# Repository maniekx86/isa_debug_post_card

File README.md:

# ISA debug post card
ISA debug post card with additional features like data/address bus analyzer, frequency measure and multi I/O POST port selection. Uses a XC95144XL CPLD as main IC. Dedicated project page with manual and assembly instructions will be available soon.

It is also designed to have a 45-degree bevel at the connector. When ordering, enable edge connector and a 45-degree bevel. Ready gerbers are available in output folder

CPLD VHDL source code and compiled firmware for the CPLD are available here: https://github.com/maniekx86/isa_debug_post_card_cpld_source

Based on https://github.com/JayesonLS/ISA-Cards IsaTemplate

## Special thanks to [PCBWay](https://www.pcbway.com)!

Special thanks to PCBWay for sponsoring this project! PCBWay is a well-known PCB prototyping and manufacturing service, providing high-quality boards and excellent customer support. I have worked with their boards in the past and can say that they are of great quality. I easily placed an order for PCBs on their platform for this project without any problems. The sponsorship also included a free quick delivery option. If you’re looking for reliable PCB prototyping and manufacturing services, I highly recommend [checking them](https://www.pcbway.com).

## Photos

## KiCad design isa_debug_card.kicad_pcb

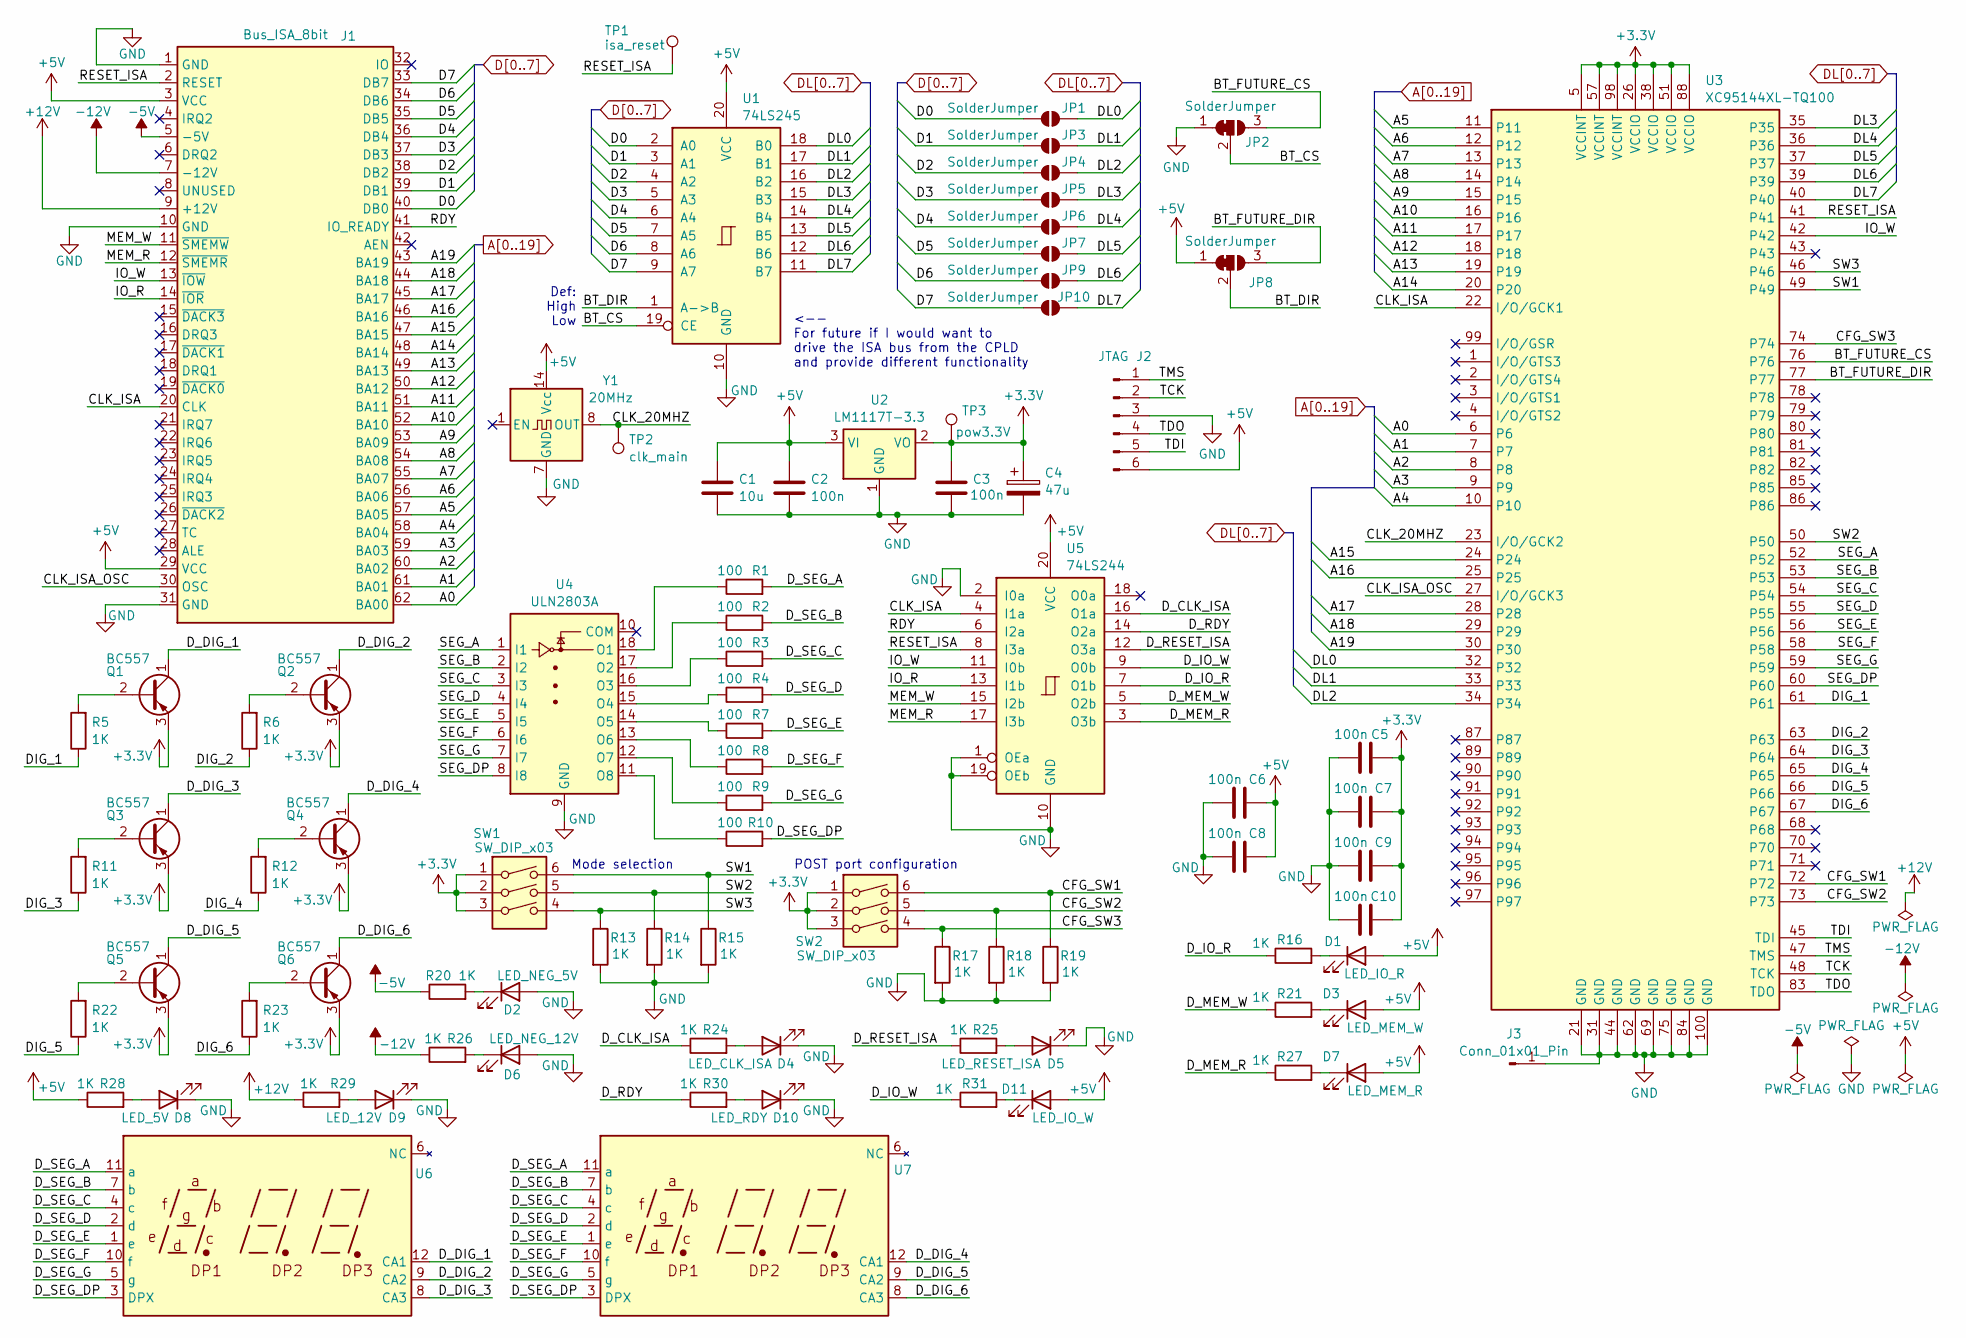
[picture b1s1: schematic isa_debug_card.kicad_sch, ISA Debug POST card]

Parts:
C1: 10u; CP_Radial_D5.0mm_P2.50mm
C2, C3, C5, C6, C7, C8, C9, C10: 100n; C_Disc_D3.0mm_W2.0mm_P2.50mm
C4: 47u; CP_Radial_D5.0mm_P2.50mm
D1: LED_IO_R; LED_D5.0mm
D2: LED_NEG_5V; LED_D5.0mm
D3: LED_MEM_W; LED_D5.0mm
D4: LED_CLK_ISA; LED_D5.0mm
D5: LED_RESET_ISA; LED_D5.0mm
D6: LED_NEG_12V; LED_D5.0mm
D7: LED_MEM_R; LED_D5.0mm
D8: LED_5V; LED_D5.0mm
D9: LED_12V; LED_D5.0mm
D10: LED_RDY; LED_D5.0mm
D11: LED_IO_W; LED_D5.0mm
J1: Bus_ISA_8bit; BUS_XT
J2: JTAG; PinSocket_1x06_P2.54mm_Vertical
J3: Conn_01x01_Pin; PinHeader_1x01_P2.54mm_Vertical
JP1, JP3, JP4, JP5, JP6, JP7, JP9, JP10: SolderJumper; SolderJumper-2_P1.3mm_Open_Pad1.0x1.5mm
JP2, JP8: SolderJumper; SolderJumper-3_P1.3mm_Bridged12_Pad1.0x1.5mm
Q1, Q2, Q3, Q4, Q5, Q6: BC557; TO-92_Inline
R1, R2, R3, R4, R7, R8, R9, R10: 100; R_Axial_DIN0204_L3.6mm_D1.6mm_P7.62mm_Horizontal
R5, R6, R11, R12, R13, R14, R15, R16, R17, R18, R19, R20, R21, R22, R23, R24, R25, R26, R27, R28, R29, R30, R31: 1K; R_Axial_DIN0204_L3.6mm_D1.6mm_P7.62mm_Horizontal
SW1, SW2: SW_DIP_x03; SW_DIP_SPSTx03_Slide_9.78x9.8mm_W7.62mm_P2.54mm
TP1: isa_reset; TestPoint_Pad_2.0x2.0mm
TP2: clk_main; TestPoint_Pad_2.0x2.0mm
TP3: pow3.3V; TestPoint_Pad_2.0x2.0mm
U1: 74LS245; DIP-20_W7.62mm
U2: LM1117T-3.3; TO-220-3_Horizontal_TabDown
U3: XC95144XL-TQ100; TQFP-100_14x14mm_P0.5mm
U4: ULN2803A; DIP-18_W7.62mm
U5: 74LS244; DIP-20_W7.62mm
U6, U7: LED_3_digit_0_56inch_12pin
Y1: 20MHz; OSC_8_14_Multi

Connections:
+3.3V: C3.1, C4.1, C5.2, C7.2, C9.2, C10.2, Q1.3 (E), Q2.3 (E), Q3.3 (E), Q4.3 (E), Q5.3 (E), Q6.3 (E), SW1.1, SW1.2, SW1.3, SW2.1, SW2.2, SW2.3, TP3.1, U2.2 (VO), U3.5 (VCCINT), U3.26 (VCCIO), U3.38 (VCCIO), U3.51 (VCCIO), U3.57 (VCCINT), U3.88 (VCCIO), U3.98 (VCCINT)
+5V: C1.1, C2.1, C6.2, C8.2, D1.2 (A), D3.2 (A), D7.2 (A), D11.2 (A), J1.3 (VCC), J1.29 (VCC), J2.6, JP8.1 (A), R28.1, U1.20 (VCC), U2.3 (VI), U5.20 (VCC), Y1.14 (Vcc)
+12V: J1.9 (+12V), R29.1
-5V: J1.5 (-5V), R20.1
-12V: J1.7 (-12V), R26.1
/BT_CS: JP2.2 (C), U1.19 (CE)
/BT_DIR: JP8.2 (C), U1.1 (A->B)
/BT_FUTURE_CS: JP2.3 (B), U3.76
/BT_FUTURE_DIR: JP8.3 (B), U3.77
/CFG_SW1: R19.1, SW2.6, U3.72
/CFG_SW2: R18.1, SW2.5, U3.73
/CFG_SW3: R17.1, SW2.4, U3.74
/CLK_20MHZ: TP2.1, U3.23 (I/O/GCK2), Y1.8 (OUT)
/CLK_ISA: J1.20 (CLK), U3.22 (I/O/GCK1), U5.4 (I1a)
/CLK_ISA_OSC: J1.30 (OSC), U3.27 (I/O/GCK3)
/DIG_1: R5.1, U3.61
/DIG_2: R6.1, U3.63
/DIG_3: R11.1, U3.64
/DIG_4: R12.1, U3.65
/DIG_5: R22.1, U3.66
/DIG_6: R23.1, U3.67
/D_CLK_ISA: R24.1, U5.16 (O1a)
/D_DIG_1: Q1.1 (C), U6.12 (CA1)
/D_DIG_2: Q2.1 (C), U6.9 (CA2)
/D_DIG_3: Q3.1 (C), U6.8 (CA3)
/D_DIG_4: Q4.1 (C), U7.12 (CA1)
/D_DIG_5: Q5.1 (C), U7.9 (CA2)
/D_DIG_6: Q6.1 (C), U7.8 (CA3)
/D_IO_R: R16.1, U5.7 (O1b)
/D_IO_W: R31.1, U5.9 (O0b)
/D_MEM_R: R27.1, U5.3 (O3b)
/D_MEM_W: R21.1, U5.5 (O2b)
/D_RDY: R30.1, U5.14 (O2a)
/D_RESET_ISA: R25.1, U5.12 (O3a)
/D_SEG_A: R1.2, U6.11 (a), U7.11 (a)
/D_SEG_B: R2.2, U6.7 (b), U7.7 (b)
/D_SEG_C: R3.2, U6.4 (c), U7.4 (c)
/D_SEG_D: R4.2, U6.2 (d), U7.2 (d)
/D_SEG_DP: R10.2, U6.3 (DPX), U7.3 (DPX)
/D_SEG_E: R7.2, U6.1 (e), U7.1 (e)
/D_SEG_F: R8.2, U6.10 (f), U7.10 (f)
/D_SEG_G: R9.2, U6.5 (g), U7.5 (g)
/IO_R: J1.14 (~IOR), U5.13 (I1b)
/IO_W: J1.13 (~IOW), U3.42, U5.11 (I0b)
/MEM_R: J1.12 (~SMEMR), U5.17 (I3b)
/MEM_W: J1.11 (~SMEMW), U5.15 (I2b)
/RDY: J1.41 (IO_READY), U5.6 (I2a)
/RESET_ISA: J1.2 (RESET), TP1.1, U3.41, U5.8 (I3a)
/SEG_A: U3.52, U4.1 (I1)
/SEG_B: U3.53, U4.2 (I2)
/SEG_C: U3.54, U4.3 (I3)
/SEG_D: U3.55, U4.4 (I4)
/SEG_DP: U3.60, U4.8 (I8)
/SEG_E: U3.56, U4.5 (I5)
/SEG_F: U3.58, U4.6 (I6)
/SEG_G: U3.59, U4.7 (I7)
/SW1: R15.1, SW1.6, U3.49
/SW2: R14.1, SW1.5, U3.50
/SW3: R13.1, SW1.4, U3.46
/TCK: J2.2, U3.48 (TCK)
/TDI: J2.5, U3.45 (TDI)
/TDO: J2.4, U3.83 (TDO)
/TMS: J2.1, U3.47 (TMS)
A0: J1.62 (BA00), U3.6
A1: J1.61 (BA01), U3.7
A2: J1.60 (BA02), U3.8
A3: J1.59 (BA03), U3.9
A4: J1.58 (BA04), U3.10
A5: J1.57 (BA05), U3.11
A6: J1.56 (BA06), U3.12
A7: J1.55 (BA07), U3.13
A8: J1.54 (BA08), U3.14
A9: J1.53 (BA09), U3.15
A10: J1.52 (BA10), U3.16
A11: J1.51 (BA11), U3.17
A12: J1.50 (BA12), U3.18
A13: J1.49 (BA13), U3.19
A14: J1.48 (BA14), U3.20
A15: J1.47 (BA15), U3.24
A16: J1.46 (BA16), U3.25
A17: J1.45 (BA17), U3.28
A18: J1.44 (BA18), U3.29
A19: J1.43 (BA19), U3.30
D0: J1.40 (DB0), JP1.1 (A), U1.2 (A0)
D1: J1.39 (DB1), JP3.1 (A), U1.3 (A1)
D2: J1.38 (DB2), JP4.1 (A), U1.4 (A2)
D3: J1.37 (DB3), JP5.1 (A), U1.5 (A3)
D4: J1.36 (DB4), JP6.1 (A), U1.6 (A4)
D5: J1.35 (DB5), JP7.1 (A), U1.7 (A5)
D6: J1.34 (DB6), JP9.1 (A), U1.8 (A6)
D7: J1.33 (DB7), JP10.1 (A), U1.9 (A7)
DL0: JP1.2 (B), U1.18 (B0), U3.32
DL1: JP3.2 (B), U1.17 (B1), U3.33
DL2: JP4.2 (B), U1.16 (B2), U3.34
DL3: JP5.2 (B), U1.15 (B3), U3.35
DL4: JP6.2 (B), U1.14 (B4), U3.36
DL5: JP7.2 (B), U1.13 (B5), U3.37
DL6: JP9.2 (B), U1.12 (B6), U3.39
DL7: JP10.2 (B), U1.11 (B7), U3.40
GND: C1.2, C2.2, C3.2, C4.2, C5.1, C6.1, C7.1, C8.1, C9.1, C10.1, D2.2 (A), D4.1 (K), D5.1 (K), D6.2 (A), D8.1 (K), D9.1 (K), D10.1 (K), J1.1 (GND), J1.10 (GND), J1.31 (GND), J2.3, J3.1, JP2.1 (A), R13.2, R14.2, R15.2, R17.2, R18.2, R19.2, U1.10 (GND), U2.1 (GND), U3.21 (GND), U3.31 (GND), U3.44 (GND), U3.62 (GND), U3.69 (GND), U3.75 (GND), U3.84 (GND), U3.100 (GND), U4.9 (GND), U5.1 (OEa), U5.2 (I0a), U5.10 (GND), U5.19 (OEb), Y1.7 (GND)
unnamed: D1.1 (K), R16.2
unnamed: D2.1 (K), R20.2
unnamed: D3.1 (K), R21.2
unnamed: D4.2 (A), R24.2
unnamed: D5.2 (A), R25.2
unnamed: D6.1 (K), R26.2
unnamed: D7.1 (K), R27.2
unnamed: D8.2 (A), R28.2
unnamed: D9.2 (A), R29.2
unnamed: D10.2 (A), R30.2
unnamed: D11.1 (K), R31.2
unnamed: Q1.2 (B), R5.2
unnamed: Q2.2 (B), R6.2
unnamed: Q3.2 (B), R11.2
unnamed: Q4.2 (B), R12.2
unnamed: Q5.2 (B), R22.2
unnamed: Q6.2 (B), R23.2
unnamed: R1.1, U4.18 (O1)
unnamed: R2.1, U4.17 (O2)
unnamed: R3.1, U4.16 (O3)
unnamed: R4.1, U4.15 (O4)
unnamed: R7.1, U4.14 (O5)
unnamed: R8.1, U4.13 (O6)
unnamed: R9.1, U4.12 (O7)
unnamed: R10.1, U4.11 (O8)

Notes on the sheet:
Def: High Low
<-- For future if I would want to drive the ISA bus from the CPLD and provide different functionality
Mode selection
POST port configuration

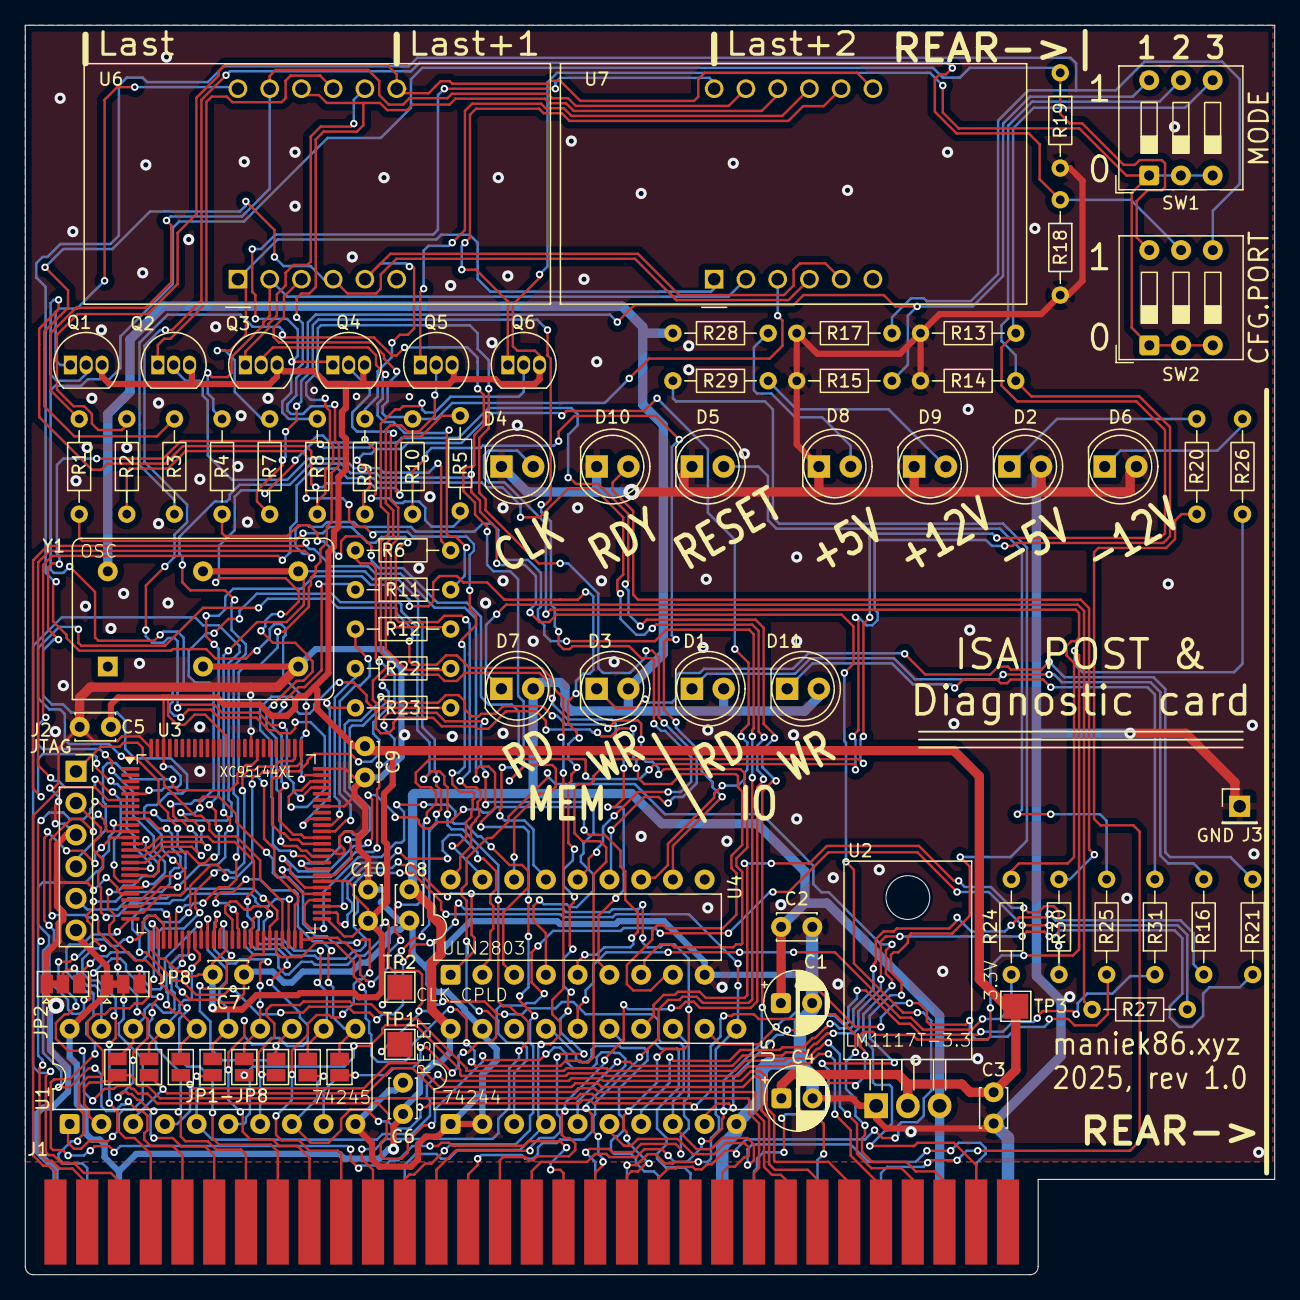
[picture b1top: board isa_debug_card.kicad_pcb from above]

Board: 2 copper layers, 99.9 x 99.9 mm, 84 parts (0 on the bottom side), 125 nets.

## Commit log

2025-06-30 Add KiCad files
2025-07-08 Update README.md (Thanks to PCBWay!)
